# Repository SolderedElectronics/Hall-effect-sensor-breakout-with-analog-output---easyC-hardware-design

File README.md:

# Hall effect sensor breakout with analog output & easyC Hardware design

## About the product

|  |
| :----------------------------------------------------------: |
|      [Buy Hall effect sensor breakout with analog output & easyC](https://www.solde.red/333082)      |

------ product description ------

## Repository contents

All Soldered Electronics hardware designed in KiCAD, and repositories are organized in the following way:

- CAD folder - contains KiCAD files (Schematics, Board, Panel Board), sorted by version. Change log lists all changes between versions.
- OUTPUTS - contains useful files, such as Bill of Materials (BOM), PDF of schematics, 3D .step file of the board and gerber files, sorted by version. 
- OUTPUTS -> Compliance - Certificates and useful legal stuff. 

## Want to contribute?

Please feel free to submit a pull request if you have any contributions. We encourage you to submit an issue or pull request if you find a bug. 

## About Soldered

At Soldered, we design and manufacture a wide selection of electronic products to help you turn your ideas into acts and bring you one step closer to your final project. Our products are intented for makers and crafted in-house by our experienced team in Osijek, Croatia. We believe that sharing is a crucial element for improvement and innovation, and we work hard to stay connected with all our makers regardless of their skill or experience level. Therefore, all our products are open-source. Finally, we always have your back. If you face any problem concerning either your shopping experience or your electronics project, our team will help you deal with it, offering efficient customer service and cost-free technical support anytime. Some of those might be useful for you:

- [Web Store](https://www.soldered.com/shop)
- [Tutorials & Projects](https://soldered.com/learn)
- [Community & Technical support](https://soldered.com/community)

## License info

All Soldered open-source hardware (OSH) is under The TAPR Open Hardware License. Read more in the LICENSE file. 

No warranty - all designs in this repository are distributed in the hope that they will be useful, but without any warranty. They are provided "AS IS", therefore without warranty of any kind, either expressed or implied. The entire quality and performance of what you do with the contents of this repository are your responsibility. In no event, Soldered Electronics will be liable for your damages, losses, including any general, special, incidental or consequential damage arising out of the use or inability to use the contents of this repository. 

## Have fun! 
And thank you from your fellow makers at Soldered Electronics.

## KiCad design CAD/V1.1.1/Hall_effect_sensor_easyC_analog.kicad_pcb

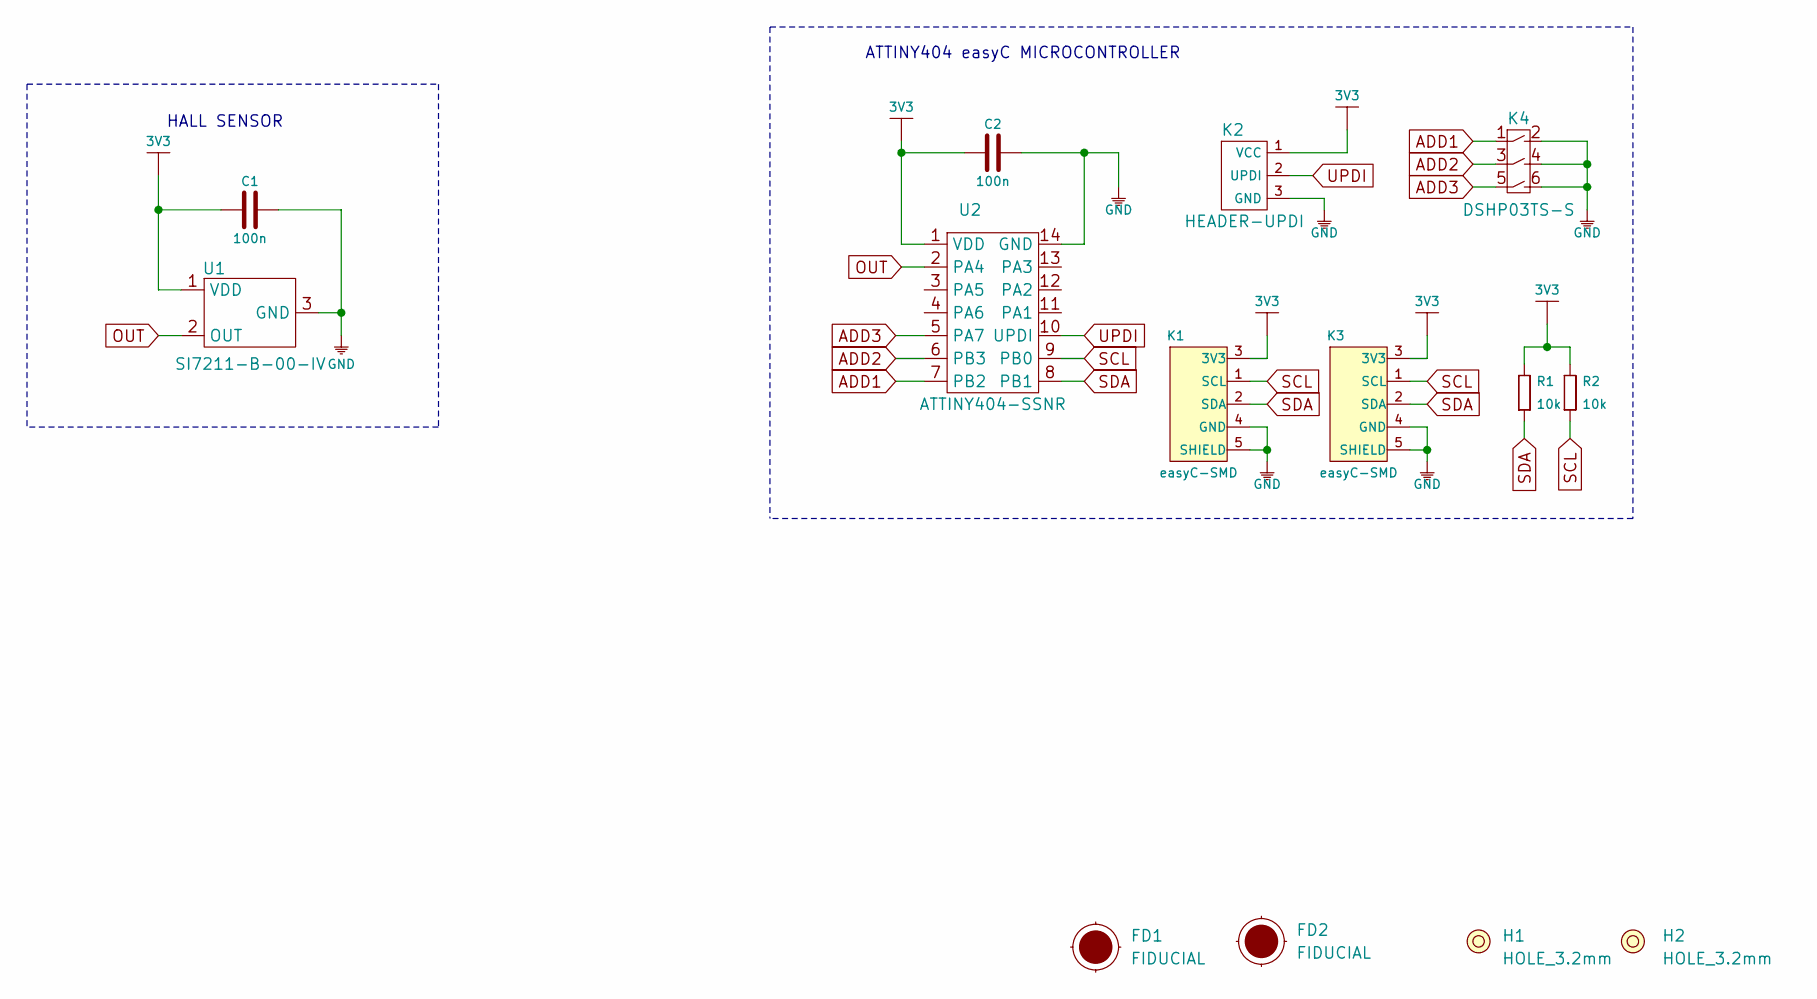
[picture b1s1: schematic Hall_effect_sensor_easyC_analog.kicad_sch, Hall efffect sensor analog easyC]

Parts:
C1, C2: 100n; 0603C
FD1, FD2: FIDUCIAL; FIDUCIAL_23
H1, H2: HOLE_3.2mm
K1, K3: easyC-SMD; easyC-connector
K2: HEADER-UPDI
K4: DSHP03TS-S
R1, R2: 10k; 0603R
U1: SI7211-B-00-IV; SOT-23-3
U2: ATTINY404-SSNR; SOIC-14

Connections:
3V3: C1.1, C2.1, K1.3 (3V3), K2.1 (VCC), K3.3 (3V3), R1.2, R2.2, U1.1 (VDD), U2.1 (VDD)
ADD1: K4.1, U2.7 (PB2)
ADD2: K4.3, U2.6 (PB3)
ADD3: K4.5, U2.5 (PA7)
GND: C1.2, C2.2, K1.4 (GND), K1.5 (SHIELD), K2.3 (GND), K3.4 (GND), K3.5 (SHIELD), K4.2, K4.4, K4.6, U1.3 (GND), U2.14 (GND)
OUT: U1.2 (OUT), U2.2 (PA4)
SCL: K1.1 (SCL), K3.1 (SCL), R2.1, U2.9 (PB0)
SDA: K1.2 (SDA), K3.2 (SDA), R1.1, U2.8 (PB1)
UPDI: K2.2 (UPDI), U2.10 (UPDI)

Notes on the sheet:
HALL SENSOR
ATTINY404 easyC MICROCONTROLLER

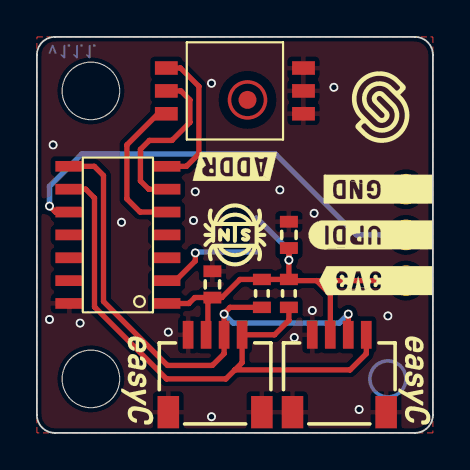
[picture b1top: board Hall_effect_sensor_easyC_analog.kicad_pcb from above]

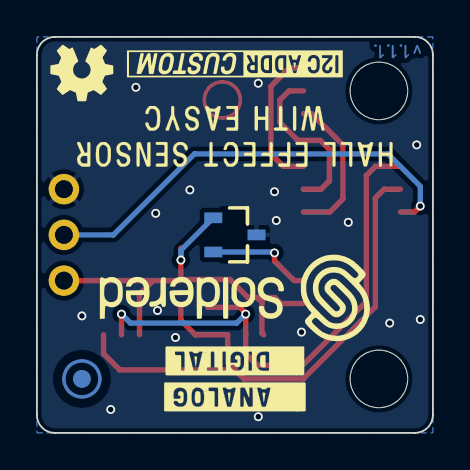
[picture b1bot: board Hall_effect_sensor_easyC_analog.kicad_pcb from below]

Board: 2 copper layers, 22.0 x 22.0 mm, 14 parts (2 on the bottom side), 9 nets.

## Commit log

2022-08-06 Updating open source files.
